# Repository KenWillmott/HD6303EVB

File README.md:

# HD6303EVB
# Hitachi HD63C03YP Evaluation Board

The HD63C03YP is a Hitachi MCU that combines a Motorola MC6803 code compatible processor, with on chip peripherals such as UART, parallel I/O, and hardware timers and counters. The MC6803 is code compatible with the MC6801, so development tools such as an assembler can be used to produce code for it. Also, existing software written for the MC6801/6803 should run on it, with few or no modifications.

The historical background is that Hitachi obtained a licence from Motorola to produce many of the devices in Motorola's 8 bit MCU catalog, which they implemented in an improved CMOS process. Many of the devices are pin compatible drop in replacements for the Motorola parts. But Hitachi also added new parts, and enhanced some of them with both documented and undocumented improvements.

The board consists of a 64 pin DIP HD63C03YP MCU, an 8k EEPROM, an external bus interface, I/O pins, and 64k SRAM. It can be interfaced from the on board serial port, running at 115200 baud and some slower baud rates. More hardware details can be found in the Wiki - https://github.com/KenWillmott/HD6303EVB/wiki.

The project is in the extreme beta stage, at the moment four working boards exist. The first and current board is designated V1.0. Some peripheral boards to plug into the expansion bus connectors, are in development. The Game Board is completed, see https://github.com/KenWillmott/M8-Game-Board/wiki

The provided ROM monitor program Kbug6303, can be written to the 8k EEPROM. Once it is installed, it is possible to perform firmware updates in place, by changing the write protect jumper on the board, and running software to copy the code from RAM to the EEPROM.

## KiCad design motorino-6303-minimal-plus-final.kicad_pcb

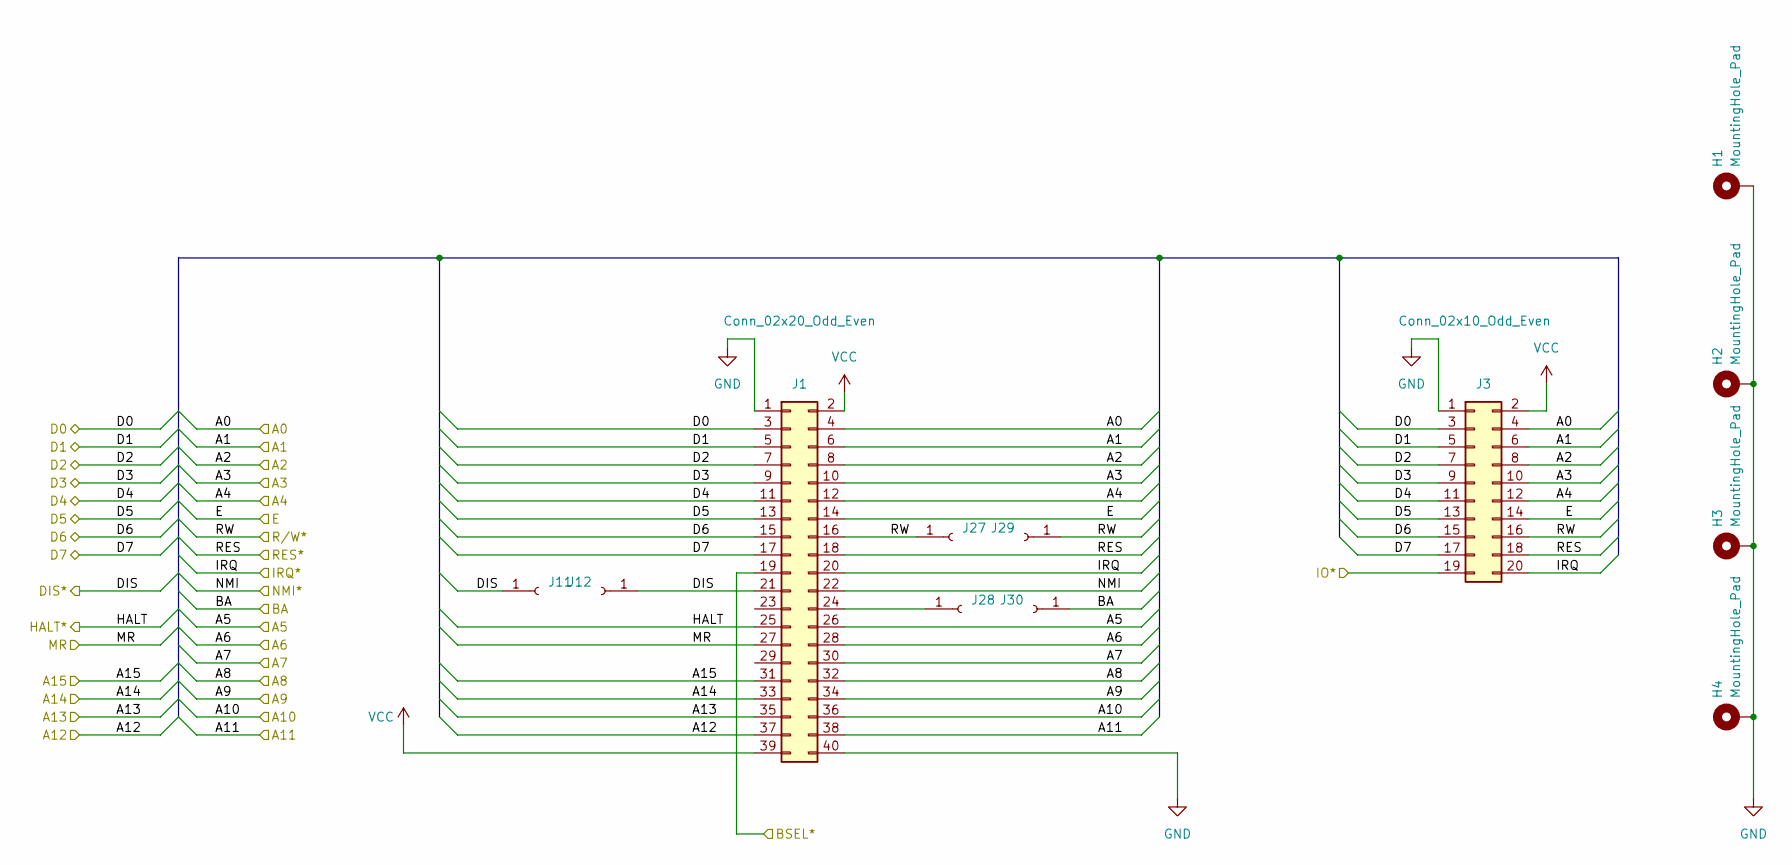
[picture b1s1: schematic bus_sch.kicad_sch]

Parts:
H1, H2, H3, H4: MountingHole_Pad; MountingHole_3.2mm_M3_Pad
J1: Conn_02x20_Odd_Even; PinSocket_2x20_P2.54mm_Vertical
J3: Conn_02x10_Odd_Even; PinSocket_2x10_P2.54mm_Vertical
J11, J12, J27, J28, J29, J30: Conn_01x01_Female; PinHeader_1x01_P2.00mm_Vertical

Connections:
/A0: J1.4, J3.4; also elsewhere on the board
/A1: J1.6, J3.6; also elsewhere on the board
/A2: J1.8, J3.8; also elsewhere on the board
/A3: J1.10, J3.10; also elsewhere on the board
/A4: J1.12, J3.12; also elsewhere on the board
/A5: J1.26; also elsewhere on the board
/A6: J1.28; also elsewhere on the board
/A7: J1.30; also elsewhere on the board
/A8: J1.32; also elsewhere on the board
/A9: J1.34; also elsewhere on the board
/A10: J1.36; also elsewhere on the board
/A11: J1.38; also elsewhere on the board
/A12: J1.37; also elsewhere on the board
/A13: J1.35; also elsewhere on the board
/A14: J1.33; also elsewhere on the board
/A15: J1.31; also elsewhere on the board
/D0: J1.3, J3.3; also elsewhere on the board
/D1: J1.5, J3.5; also elsewhere on the board
/D2: J1.7, J3.7; also elsewhere on the board
/D3: J1.9, J3.9; also elsewhere on the board
/D4: J1.11, J3.11; also elsewhere on the board
/D5: J1.13, J3.13; also elsewhere on the board
/D6: J1.15, J3.15; also elsewhere on the board
/D7: J1.17, J3.17; also elsewhere on the board
/PIRQ*: J1.20, J3.20; also elsewhere on the board
BA: J30.1; also elsewhere on the board
BSEL*: J1.19; also elsewhere on the board
DIS*: J1.21, J11.1, J12.1; also elsewhere on the board
E: J1.14, J3.14; also elsewhere on the board
GND: H1.1, H2.1, H3.1, H4.1, J1.1, J1.40, J3.1; also elsewhere on the board
HALT*: J1.25; also elsewhere on the board
IOSEL*: J3.19; also elsewhere on the board
MR: J1.27; also elsewhere on the board
NMI*: J1.22; also elsewhere on the board
unnamed: J1.24, J28.1
RES*: J1.18, J3.18; also elsewhere on the board
R/W*: J1.16, J3.16, J27.1, J29.1; also elsewhere on the board
VCC: J1.2, J1.39, J3.2; also elsewhere on the board

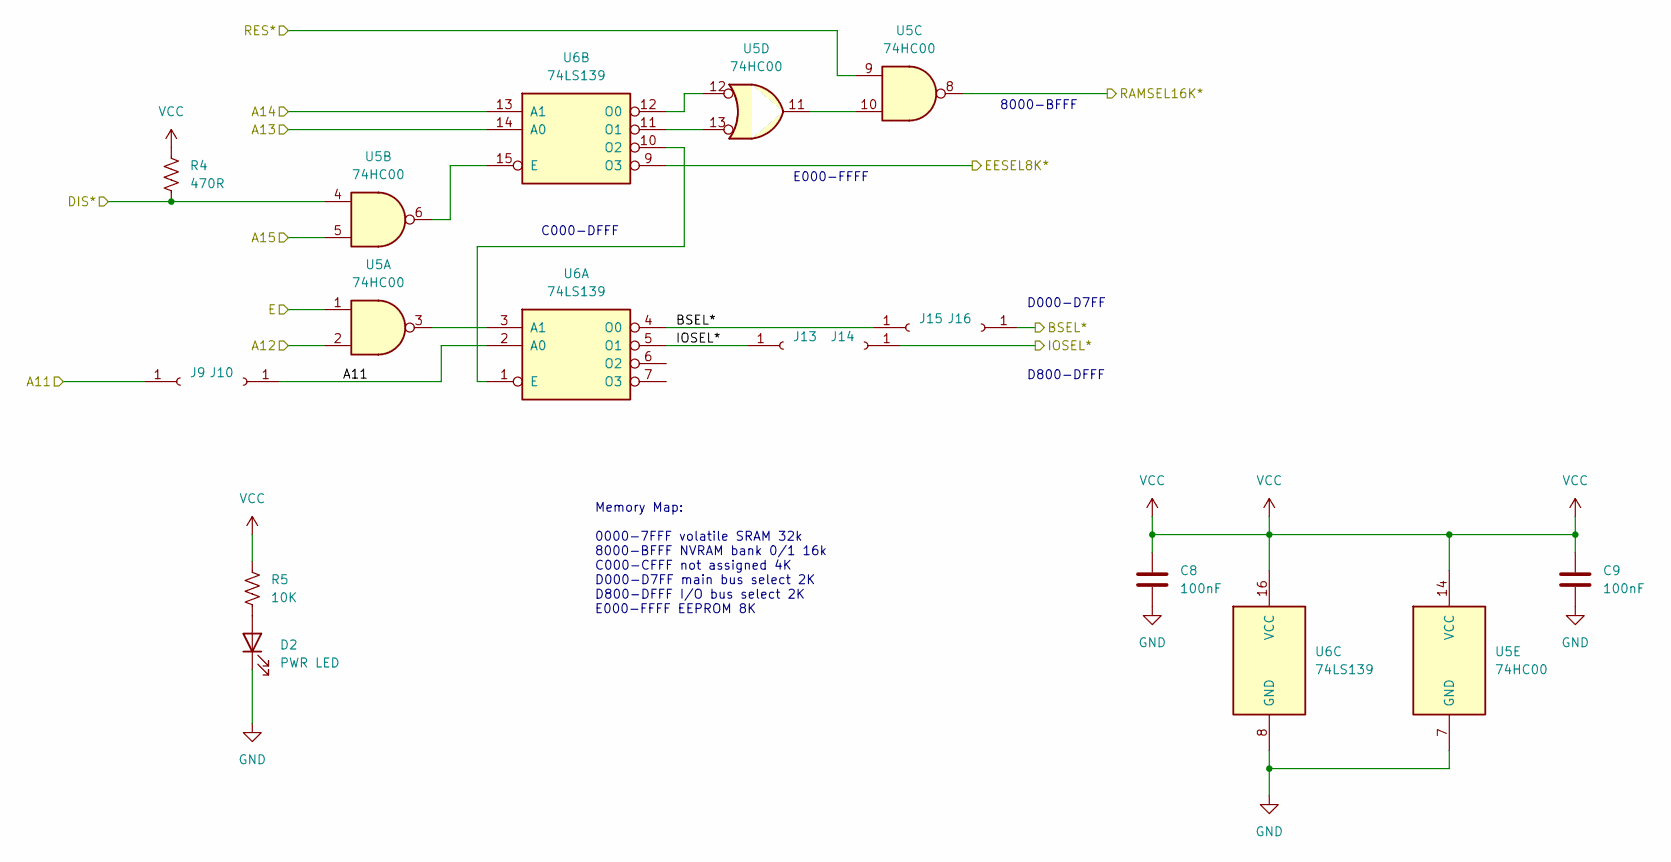
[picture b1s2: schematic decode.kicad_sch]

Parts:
C8, C9: 100nF; C_Disc_D8.0mm_W5.0mm_P5.00mm
D2: PWR LED; LED_D3.0mm
J9, J10, J13, J14, J15, J16: Conn_01x01_Female; PinHeader_1x01_P2.00mm_Vertical
R4: 470R; R_Axial_DIN0207_L6.3mm_D2.5mm_P10.16mm_Horizontal
R5: 10K; R_Axial_DIN0207_L6.3mm_D2.5mm_P10.16mm_Horizontal
U5: 74HC00; DIP-14_W7.62mm
U6: 74LS139; DIP-16_W7.62mm

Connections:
/A11: J9.1, J10.1, U6.2 (A0); also elsewhere on the board
/A12: U5.2; also elsewhere on the board
/A13: U6.14 (A0); also elsewhere on the board
/A14: U6.13 (A1); also elsewhere on the board
/A15: U5.5; also elsewhere on the board
/EESEL8K*: U6.9 (O3); also elsewhere on the board
/decode/RAMSEL16K*: U5.8; also elsewhere on the board
BSEL*: J15.1, J16.1, U6.4 (O0); also elsewhere on the board
DIS*: R4.2, U5.4; also elsewhere on the board
E: U5.1; also elsewhere on the board
GND: C8.2, C9.2, D2.1 (K), U5.7 (GND), U6.8 (GND); also elsewhere on the board
IOSEL*: J13.1, J14.1, U6.5 (O1); also elsewhere on the board
unnamed: D2.2 (A), R5.2
unnamed: U5.3, U6.3 (A1)
unnamed: U5.6, U6.15 (E)
unnamed: U5.10, U5.11
unnamed: U5.12, U6.12 (O0)
unnamed: U5.13, U6.11 (O1)
unnamed: U6.1 (E), U6.10 (O2)
RES*: U5.9; also elsewhere on the board
VCC: C8.1, C9.1, R4.1, R5.1, U5.14 (VCC), U6.16 (VCC); also elsewhere on the board

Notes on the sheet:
D800-DFFF
C000-DFFF
Memory Map: 0000-7FFF volatile SRAM 32k 8000-BFFF NVRAM bank 0/1 16k C000-CFFF not assigned 4K D000-D7FF main bus select 2K D800-DFFF I/O bus select 2K E000-FFFF EEPROM 8K
D000-D7FF
E000-FFFF
8000-BFFF

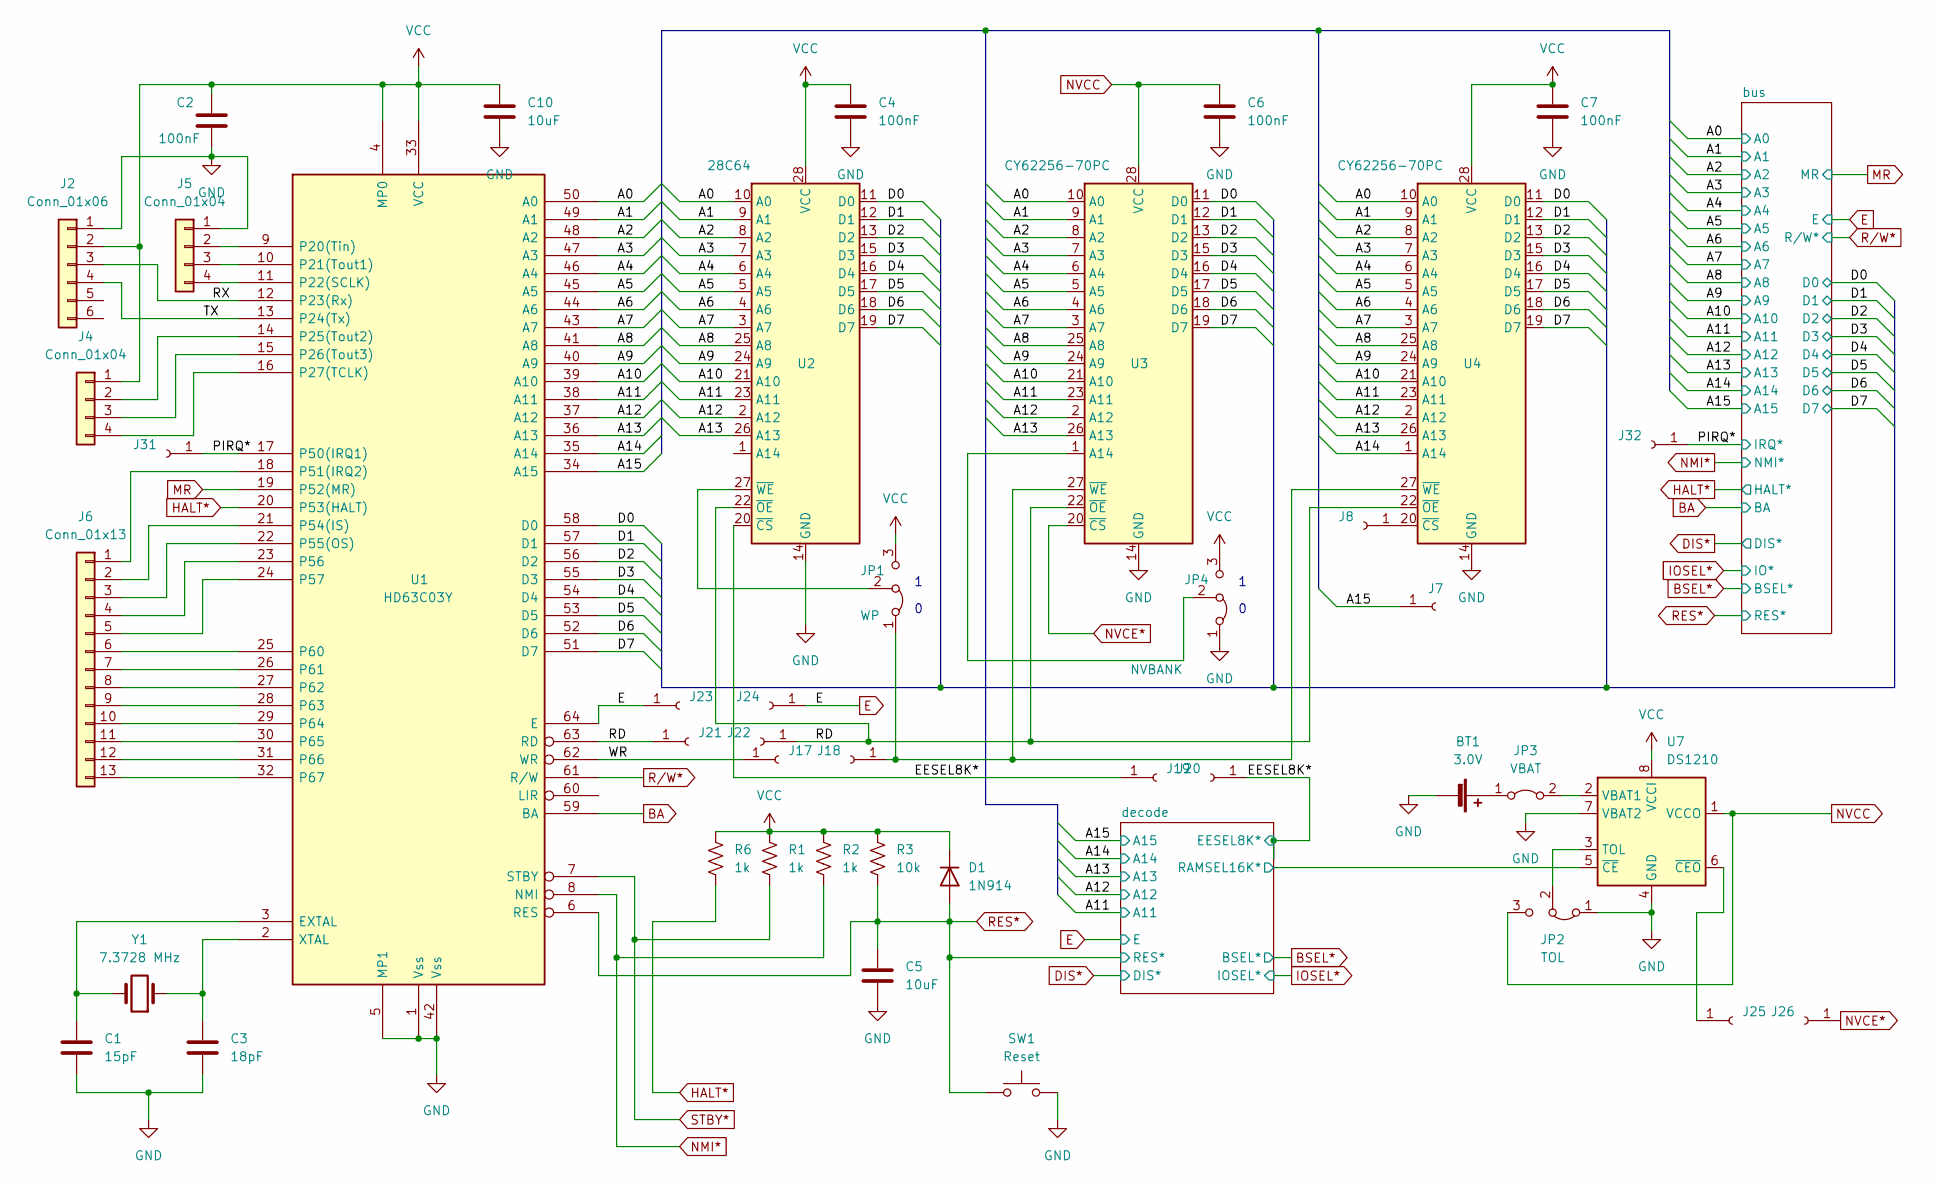
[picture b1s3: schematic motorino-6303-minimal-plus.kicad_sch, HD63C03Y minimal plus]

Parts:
BT1: 3.0V; BatteryHolder_Keystone_103_1x20mm
C1: 15pF; C_Disc_D8.0mm_W5.0mm_P5.00mm
C2, C4, C6, C7: 100nF; C_Disc_D8.0mm_W5.0mm_P5.00mm
C3: 18pF; C_Disc_D8.0mm_W5.0mm_P5.00mm
C5, C10: 10uF; C_Disc_D8.0mm_W5.0mm_P5.00mm
D1: 1N914; D_DO-35_SOD27_P7.62mm_Horizontal
J2: Conn_01x06; PinSocket_1x06_P2.00mm_Vertical
J4, J5: Conn_01x04; PinHeader_1x04_P2.54mm_Vertical
J6: Conn_01x13; PinHeader_1x13_P2.54mm_Vertical
J7, J8: (no value)
J17, J18, J19, J20, J21, J22, J23, J24, J25, J26, J31, J32: Conn_01x01_Female; PinHeader_1x01_P2.00mm_Vertical
JP1: WP; PinHeader_1x03_P2.54mm_Vertical
JP2: TOL; PinHeader_1x03_P2.54mm_Vertical
JP3: VBAT; PinHeader_2x01_P2.54mm_Vertical
JP4: NVBANK; PinHeader_1x03_P2.54mm_Vertical
R1, R2, R6: 1k; R_Axial_DIN0207_L6.3mm_D2.5mm_P10.16mm_Horizontal
R3: 10k; R_Axial_DIN0207_L6.3mm_D2.5mm_P10.16mm_Horizontal
SW1: Reset; SW_PUSH_6mm_H5mm
U1: HD63C03Y; DIP-64_HD63C03
U2: 28C64; DIP-28_W15.24mm_Socket
U3, U4: CY62256-70PC; DIP-28_W15.24mm
U7: DS1210; DIP-8_W7.62mm
Y1: 7.3728 MHz; Crystal_HC49-U_Vertical

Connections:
/A0: U1.50 (A0), U2.10 (A0), U3.10 (A0), U4.10 (A0); also elsewhere on the board
/A1: U1.49 (A1), U2.9 (A1), U3.9 (A1), U4.9 (A1); also elsewhere on the board
/A2: U1.48 (A2), U2.8 (A2), U3.8 (A2), U4.8 (A2); also elsewhere on the board
/A3: U1.47 (A3), U2.7 (A3), U3.7 (A3), U4.7 (A3); also elsewhere on the board
/A4: U1.46 (A4), U2.6 (A4), U3.6 (A4), U4.6 (A4); also elsewhere on the board
/A5: U1.45 (A5), U2.5 (A5), U3.5 (A5), U4.5 (A5); also elsewhere on the board
/A6: U1.44 (A6), U2.4 (A6), U3.4 (A6), U4.4 (A6); also elsewhere on the board
/A7: U1.43 (A7), U2.3 (A7), U3.3 (A7), U4.3 (A7); also elsewhere on the board
/A8: U1.41 (A8), U2.25 (A8), U3.25 (A8), U4.25 (A8); also elsewhere on the board
/A9: U1.40 (A9), U2.24 (A9), U3.24 (A9), U4.24 (A9); also elsewhere on the board
/A10: U1.39 (A10), U2.21 (A10), U3.21 (A10), U4.21 (A10); also elsewhere on the board
/A11: U1.38 (A11), U2.23 (A11), U3.23 (A11), U4.23 (A11); also elsewhere on the board
/A12: U1.37 (A12), U2.2 (A12), U3.2 (A12), U4.2 (A12); also elsewhere on the board
/A13: U1.36 (A13), U2.26 (A13), U3.26 (A13), U4.26 (A13); also elsewhere on the board
/A14: U1.35 (A14), U4.1 (A14); also elsewhere on the board
/A15: J7.1, U1.34 (A15); also elsewhere on the board
/D0: U1.58 (D0), U2.11 (D0), U3.11 (D0), U4.11 (D0); also elsewhere on the board
/D1: U1.57 (D1), U2.12 (D1), U3.12 (D1), U4.12 (D1); also elsewhere on the board
/D2: U1.56 (D2), U2.13 (D2), U3.13 (D2), U4.13 (D2); also elsewhere on the board
/D3: U1.55 (D3), U2.15 (D3), U3.15 (D3), U4.15 (D3); also elsewhere on the board
/D4: U1.54 (D4), U2.16 (D4), U3.16 (D4), U4.16 (D4); also elsewhere on the board
/D5: U1.53 (D5), U2.17 (D5), U3.17 (D5), U4.17 (D5); also elsewhere on the board
/D6: U1.52 (D6), U2.18 (D6), U3.18 (D6), U4.18 (D6); also elsewhere on the board
/D7: U1.51 (D7), U2.19 (D7), U3.19 (D7), U4.19 (D7); also elsewhere on the board
/EESEL8K*: J19.1, J20.1, U2.20 (~CS); also elsewhere on the board
/PIRQ*: J31.1, J32.1, U1.17 (P50(IRQ1)); also elsewhere on the board
/RD: J21.1, J22.1, U1.63 (RD), U2.22 (~OE), U3.22 (~OE), U4.22 (~OE)
/RX: J2.3, U1.12 (P23(Rx))
/TX: J2.4, U1.13 (P24(Tx))
/WR: J17.1, U1.62 (WR)
/decode/RAMSEL16K*: U7.5 (~CE); also elsewhere on the board
BA: U1.59 (BA); also elsewhere on the board
E: J23.1, J24.1, U1.64 (E); also elsewhere on the board
GND: BT1.2 (-), C1.2, C2.2, C3.2, C4.2, C5.2, C6.2, C7.2, C10.2, J2.1, J5.1, JP2.1 (A), JP4.1 (A), SW1.2, U1.1 (Vss), U1.5 (MP1), U1.42 (Vss), U2.14 (GND), U3.14 (GND), U4.14 (GND), U7.4 (GND), U7.7 (VBAT2); also elsewhere on the board
HALT*: R6.2, U1.20 (P53(HALT)); also elsewhere on the board
MR: U1.19 (P52(MR)); also elsewhere on the board
NMI*: R2.2, U1.8 (NMI); also elsewhere on the board
NVCC: C6.1, JP2.3 (B), U3.28 (VCC), U7.1 (VCCO)
NVCE*: J26.1, U3.20 (~CS)
unnamed: BT1.1 (+), JP3.1 (A)
unnamed: C1.1, U1.3 (EXTAL), Y1.2
unnamed: C3.1, U1.2 (XTAL), Y1.1
unnamed: J4.2, U1.14 (P25(Tout2))
unnamed: J4.3, U1.15 (P26(Tout3))
unnamed: J4.4, U1.16 (P27(TCLK))
unnamed: J5.2, U1.9 (P20(Tin))
unnamed: J5.3, U1.10 (P21(Tout1))
unnamed: J5.4, U1.11 (P22(SCLK))
unnamed: J6.1, U1.18 (P51(IRQ2))
unnamed: J6.2, U1.21 (P54(IS))
unnamed: J6.3, U1.22 (P55(OS))
unnamed: J6.4, U1.23 (P56)
unnamed: J6.5, U1.24 (P57)
unnamed: J6.6, U1.25 (P60)
unnamed: J6.7, U1.26 (P61)
unnamed: J6.8, U1.27 (P62)
unnamed: J6.9, U1.28 (P63)
unnamed: J6.10, U1.29 (P64)
unnamed: J6.11, U1.30 (P65)
unnamed: J6.12, U1.31 (P66)
unnamed: J6.13, U1.32 (P67)
unnamed: J8.1, U4.20 (~CS)
unnamed: J18.1, JP1.1 (A), U3.27 (~WE), U4.27 (~WE)
unnamed: JP1.2 (C), U2.27 (~WE)
unnamed: JP2.2 (C), U7.3 (TOL)
unnamed: JP3.2 (B), U7.2 (VBAT1)
unnamed: JP4.2 (C), U3.1 (A14)
unnamed: J25.1, U7.6 (~CEO)
RES*: C5.1, D1.2 (A), R3.2, SW1.1, U1.6 (RES); also elsewhere on the board
R/W*: U1.61 (R/W); also elsewhere on the board
STBY*: R1.2, U1.7 (STBY)
VCC: C2.1, C4.1, C7.1, C10.1, D1.1 (K), J2.2, J4.1, JP1.3 (B), JP4.3 (B), R1.1, R2.1, R3.1, R6.1, U1.4 (MP0), U1.33 (VCC), U2.28 (VCC), U4.28 (VCC), U7.8 (VCCI); also elsewhere on the board

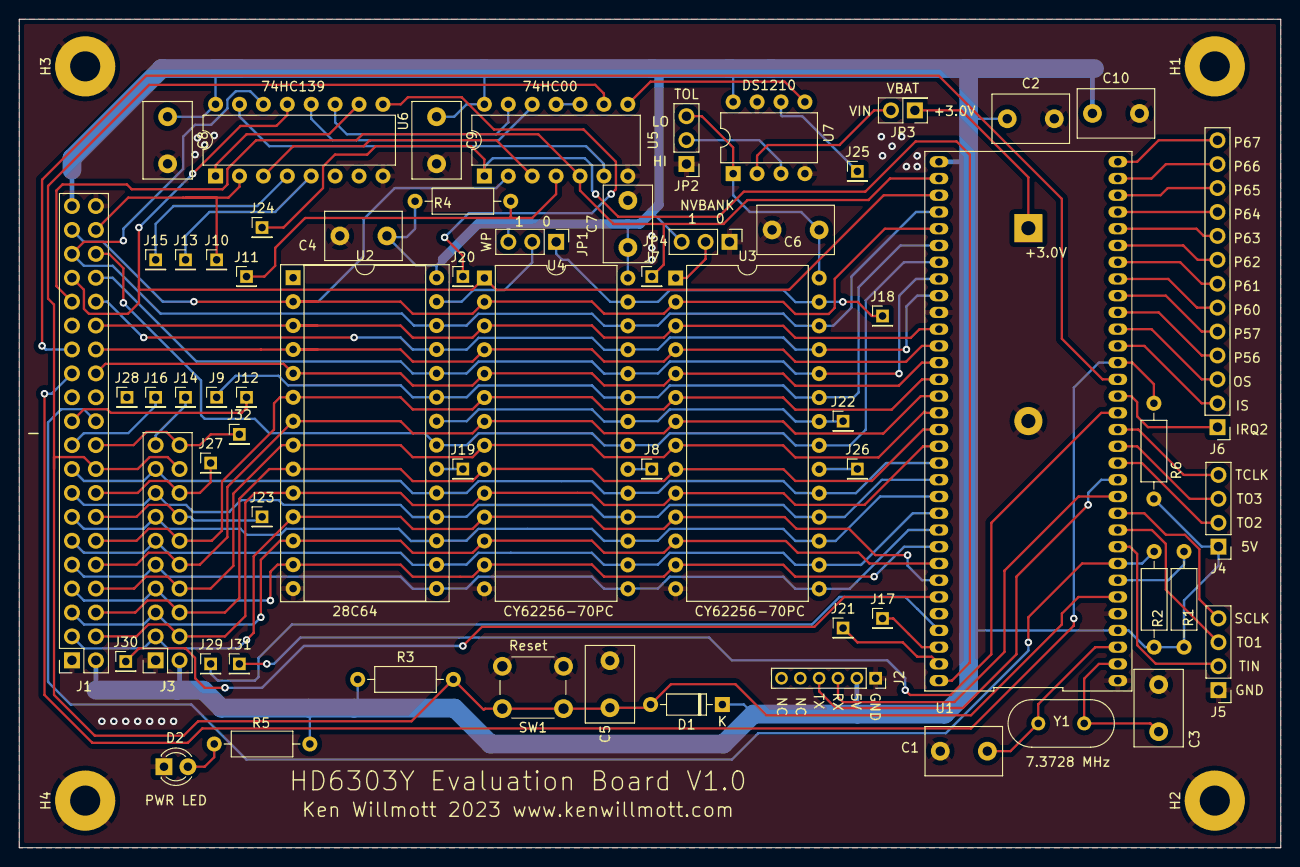
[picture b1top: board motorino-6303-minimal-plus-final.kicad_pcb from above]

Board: 2 copper layers, 134.0 x 88.0 mm, 68 parts (1 on the bottom side), 83 nets.

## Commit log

2023-05-21 Monitor program, upgraded
2023-05-22 Completed board image
2023-07-15 Monitor update to 1.03
2023-07-17 Utility code from Hitachi HD6301-3 Handbook
2023-07-19 Monitor Firmware - v. 1.03
    This version is ported from the Motorola standard assembler, to the ASxxxx macro assembler by Alan Baldwin. All my development will use it from now on, if only because it supports the HD6303 extra in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
2023-07-21 PCF8584 interface code NON WORKING!!!!
    Motorola assembler format.
2023-07-21 Hitachi math code - ASX assembler version
2023-09-20 Next generation HD6303Y board schematic
    Might be split into separate boards, but this logic will remain.
